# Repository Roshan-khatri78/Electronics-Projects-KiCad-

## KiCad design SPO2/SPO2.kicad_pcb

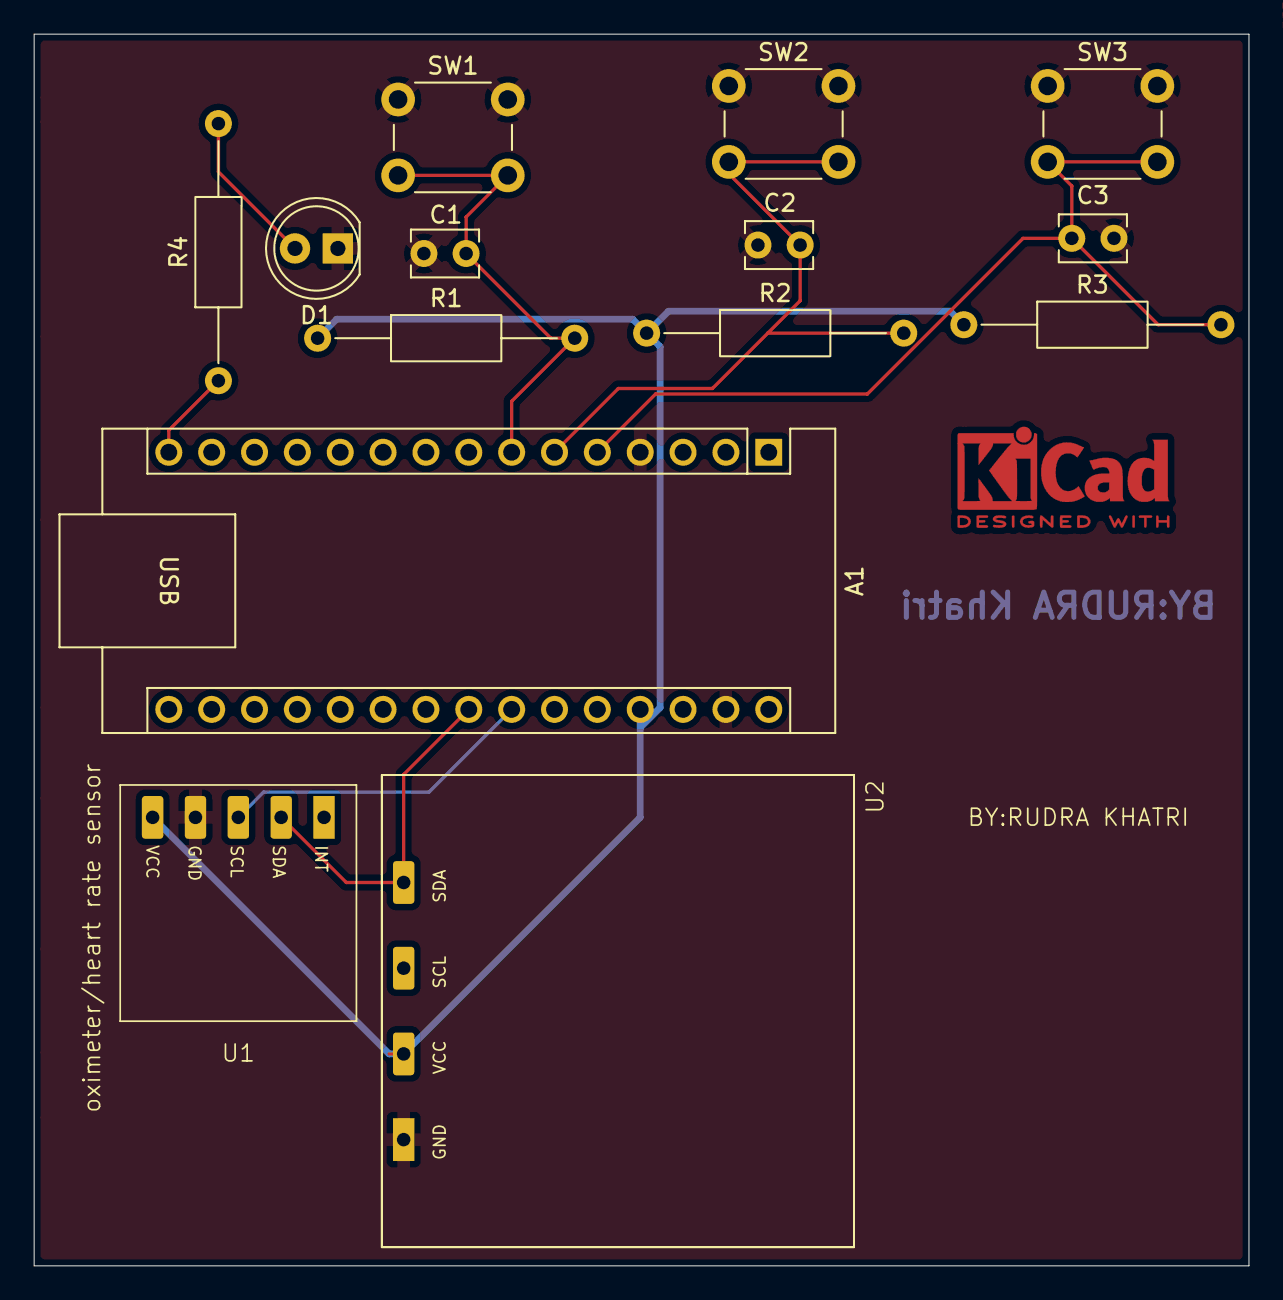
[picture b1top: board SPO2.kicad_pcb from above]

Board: 4 copper layers, 72.0 x 73.0 mm, 14 parts (0 on the bottom side), 9 nets.

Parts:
A1: Arduino_Nano_v3.x; Arduino_Nano
C1, C2, C3: 100n; C_Disc_D3.8mm_W2.6mm_P2.50mm
D1: LED; LED_D5.0mm
R1, R2, R3, R4: 1k; R_Axial_DIN0207_L6.3mm_D2.5mm_P15.24mm_Horizontal
SW1, SW2, SW3: SW_Push; SW_PUSH_6mm
U1: Max30102; MAX30102_Module
U2: SSD1306

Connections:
+5V: A1.27 (+5V), R1.1, R2.1, R3.1, U1.5 (VCC), U2.2 (VCC)
/SCL: A1.24 (A5), U1.3 (SCL)
GND: A1.4 (GND), A1.29 (GND), C1.2, C2.2, C3.2, D1.1 (K), SW1.1, SW2.1, SW3.1, U1.4 (GND), U2.1 (GND)
unnamed: A1.23 (A4), U1.2 (SDA), U2.4 (SDA)
unnamed: A1.5 (D2), C3.1, R3.2, SW3.2
unnamed: A1.6 (D3), C2.1, R2.2, SW2.2
unnamed: A1.7 (D4), C1.1, R1.2, SW1.2
unnamed: A1.15 (D12), R4.1
unnamed: D1.2 (A), R4.2

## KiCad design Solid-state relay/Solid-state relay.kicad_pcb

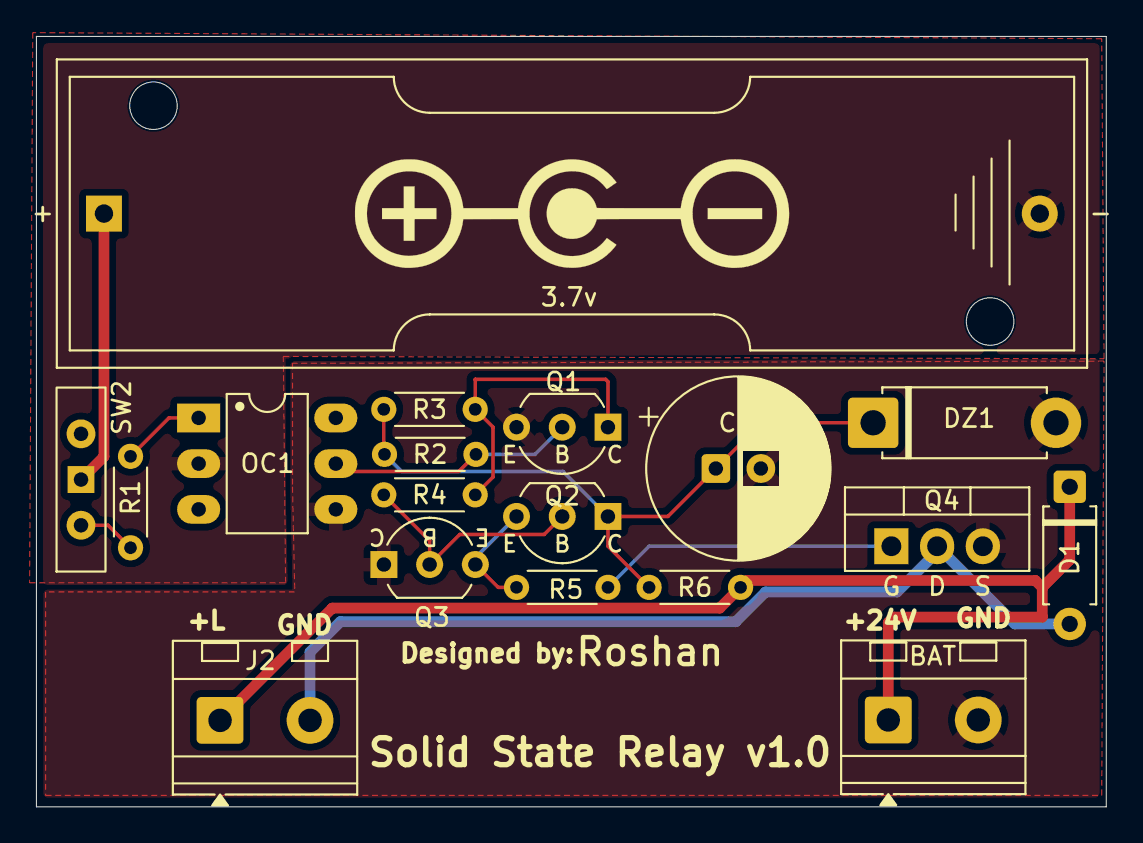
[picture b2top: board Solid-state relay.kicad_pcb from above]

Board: 4 copper layers, 59.4 x 42.8 mm, 18 parts (0 on the bottom side), 13 nets.

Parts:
3.7v: 3.7v; BatteryHolder_Keystone_2460_1xAA
BAT: Screw_Terminal_01x02; TerminalBlock_MetzConnect_Type094_RT03502HBLU_1x02_P5.00mm_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
C1: 10uf/10v; CP_Radial_D10.0mm_P2.50mm
D1: 1N4007; D_A-405_P7.62mm_Horizontal
DZ1: D_Zener_Generic; D_5W_P10.16mm_Horizontal
J2: Screw_Terminal_01x02; TerminalBlock_MetzConnect_Type094_RT03502HBLU_1x02_P5.00mm_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
OC1: MCT2EM; DIP-6_W7.62mm_LongPads
Q1: BC548; TO-92_Inline_Wide_CBE
Q2: BC547; TO-92_Inline_Wide_CBE
Q3: BC557; TO-92_Inline_Wide_CBE
Q4: IRF540; TO-220-3_Vertical_GDS
R1: 220; R_Axial_DIN0204_L3.6mm_D1.6mm_P5.08mm_Horizontal
R2: 10k; R_Axial_DIN0204_L3.6mm_D1.6mm_P5.08mm_Horizontal
R3, R4: 1k; R_Axial_DIN0204_L3.6mm_D1.6mm_P5.08mm_Horizontal
R5, R6: 100; R_Axial_DIN0204_L3.6mm_D1.6mm_P5.08mm_Horizontal
SW2: SW_Wuerth_450301014042; SW_Slide-03_Wuerth-WS-SLTV_10x2.5x6.4_P2.54mm

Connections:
/+: BAT.1, D1.1 (K), J2.1, R6.2
/A: D1.2 (A), J2.2, Q4.2 (D)
GND_CTRL: 3.7v.2 (-), OC1.2
GND_PWR: BAT.2, C1.2, DZ1.2 (A), OC1.4, Q1.3 (E), Q3.1 (C), Q4.3 (S)
unnamed: 3.7v.1 (+), SW2.1 (B)
unnamed: C1.1, DZ1.1 (K), Q2.1 (C), R2.1, R3.1, R6.1
unnamed: OC1.1, R1.2
unnamed: OC1.5, Q1.2 (B), R2.2
unnamed: Q1.1 (C), R3.2, R4.1
unnamed: Q2.2 (B), Q3.2 (B), R4.2
unnamed: Q2.3 (E), Q3.3 (E), R5.1
unnamed: Q4.1 (G), R5.2
unnamed: R1.1, SW2.2 (C)

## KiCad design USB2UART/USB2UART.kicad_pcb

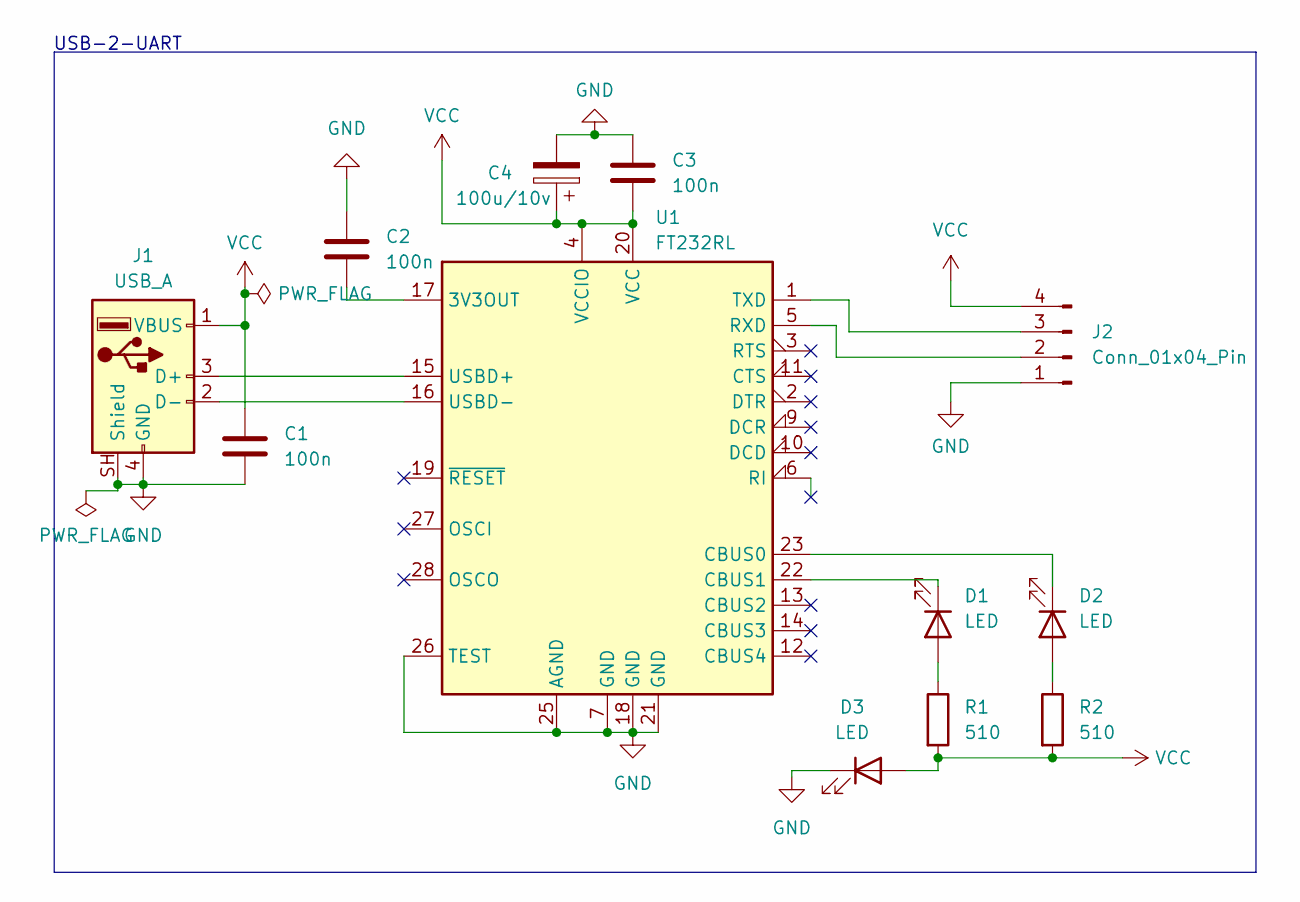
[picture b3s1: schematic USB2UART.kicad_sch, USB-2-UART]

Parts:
C1, C2, C3: 100n; C_Disc_D6.0mm_W2.5mm_P5.00mm
C4: 100u/10v; CP_Radial_D5.0mm_P2.00mm
D1, D2, D3: LED; LED_D3.0mm
J1: USB_A; USB_A_Connfly_DS1095
J2: Conn_01x04_Pin; PinHeader_1x04_P2.00mm_Vertical
R1, R2: 510; R_Axial_DIN0204_L3.6mm_D1.6mm_P5.08mm_Horizontal
U1: FT232RL; SSOP-28_5.3x10.2mm_P0.65mm

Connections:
GND: C1.2, C2.1, C3.1, C4.2, D3.1 (K), J1.4 (GND), J1.SH (Shield), J2.1, U1.7 (GND), U1.18 (GND), U1.21 (GND), U1.25 (AGND), U1.26 (TEST)
unnamed: D1.2 (A), R1.1
unnamed: D1.1 (K), U1.22 (CBUS1)
unnamed: D2.2 (A), R2.1
unnamed: D2.1 (K), U1.23 (CBUS0)
unnamed: J1.3 (D+), U1.15 (USBD+)
unnamed: J1.2 (D-), U1.16 (USBD-)
unnamed: J2.2, U1.5 (RXD)
unnamed: J2.3, U1.1 (TXD)
unnamed: C2.2, U1.17 (3V3OUT)
VCC: C1.1, C3.2, C4.1, D3.2 (A), J1.1 (VBUS), J2.4, R1.2, R2.2, U1.4 (VCCIO), U1.20 (VCC)

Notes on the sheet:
USB-2-UART

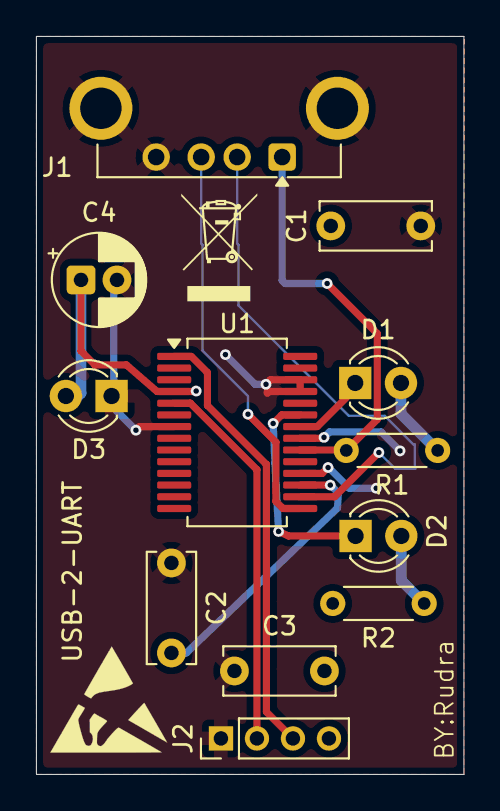
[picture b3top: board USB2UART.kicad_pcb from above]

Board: 4 copper layers, 23.8 x 41.0 mm, 12 parts (0 on the bottom side), 11 nets.

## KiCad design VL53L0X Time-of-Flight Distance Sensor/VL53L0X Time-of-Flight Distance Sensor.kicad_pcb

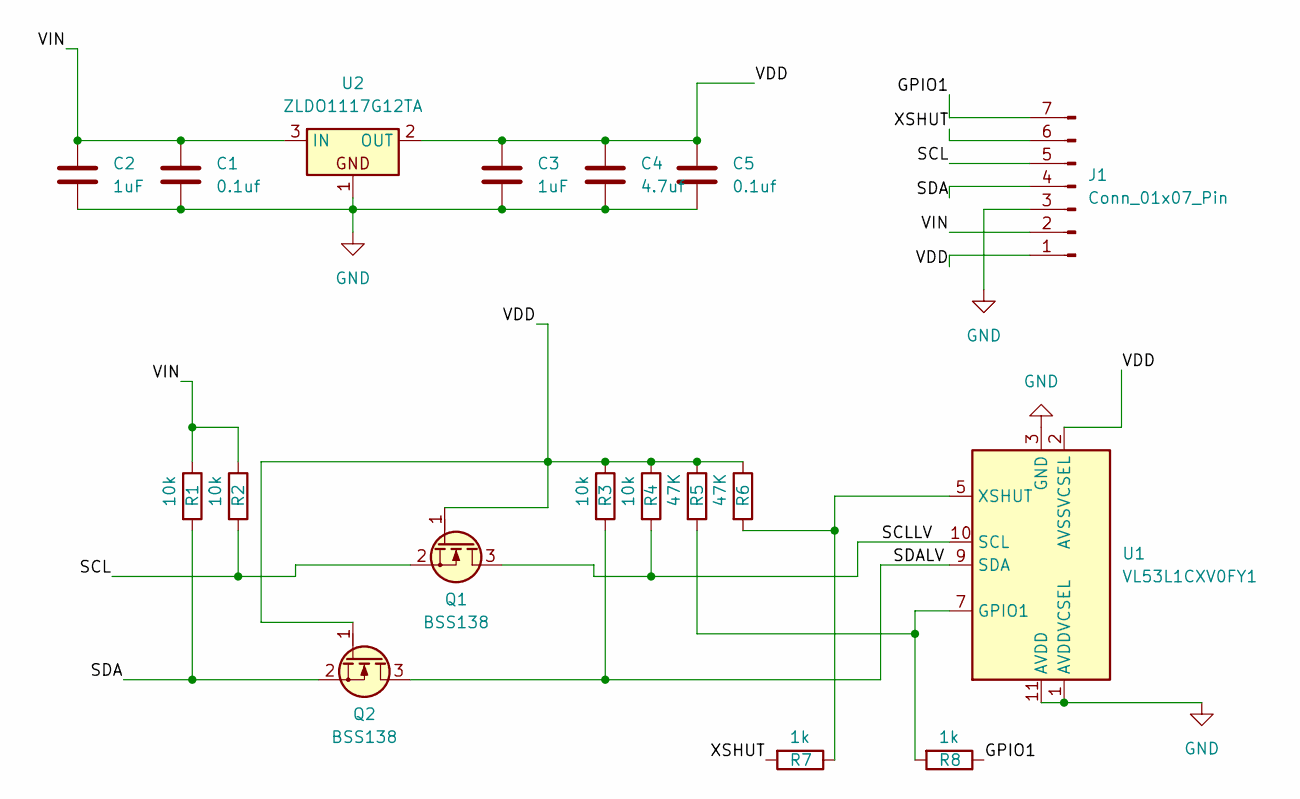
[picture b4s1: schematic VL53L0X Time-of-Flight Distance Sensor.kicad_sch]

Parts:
C1, C5: 0.1uf; C_0402_1005Metric_Pad0.74x0.62mm_HandSolder
C2, C3: 1uF; C_0402_1005Metric_Pad0.74x0.62mm_HandSolder
C4: 4.7uf; C_0402_1005Metric_Pad0.74x0.62mm_HandSolder
J1: Conn_01x07_Pin; PinHeader_1x07_P2.54mm_Horizontal
Q1, Q2: BSS138; SOT-23
R1, R2, R3, R4: 10k; R_0201_0603Metric
R5, R6: 47K; R_0201_0603Metric
R7, R8: 1k; R_0805_2012Metric
U1: VL53L1CXV0FY1; ST_VL53L1x
U2: ZLDO1117G12TA; SOT-323_SC-70

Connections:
/GPIO1: J1.7, R8.1
/SCL: J1.5, Q1.2 (S), R2.2
/SCLLV: Q1.3 (D), R4.2, U1.10 (SCL)
/SDA: J1.4, Q2.2 (S), R1.2
/SDALV: Q2.3 (D), R3.2, U1.9 (SDA)
/VDD: C3.1, C4.1, C5.1, J1.1, Q1.1 (G), Q2.1 (G), R3.1, R4.1, R5.1, R6.1, U1.2 (AVSSVCSEL), U2.2 (OUT)
/VIN: C1.1, C2.1, J1.2, R1.1, R2.1, U2.3 (IN)
/XSHUT: J1.6, R7.2
GND: C1.2, C2.2, C3.2, C4.2, C5.2, J1.3, U1.1 (AVDDVCSEL), U1.3 (GND), U1.4 (GND), U1.6 (GND), U1.11 (AVDD), U1.12 (GND), U2.1
unnamed: R5.2, R8.2, U1.7 (GPIO1)
unnamed: R6.2, R7.1, U1.5 (XSHUT)

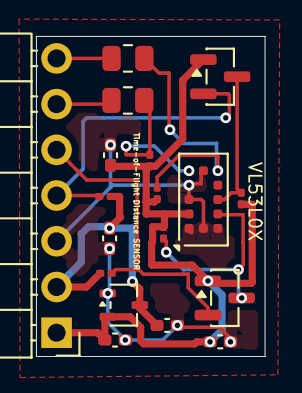
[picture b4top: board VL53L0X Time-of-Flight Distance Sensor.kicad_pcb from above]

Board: 2 copper layers, 12.7 x 17.8 mm, 18 parts (0 on the bottom side), 11 nets.

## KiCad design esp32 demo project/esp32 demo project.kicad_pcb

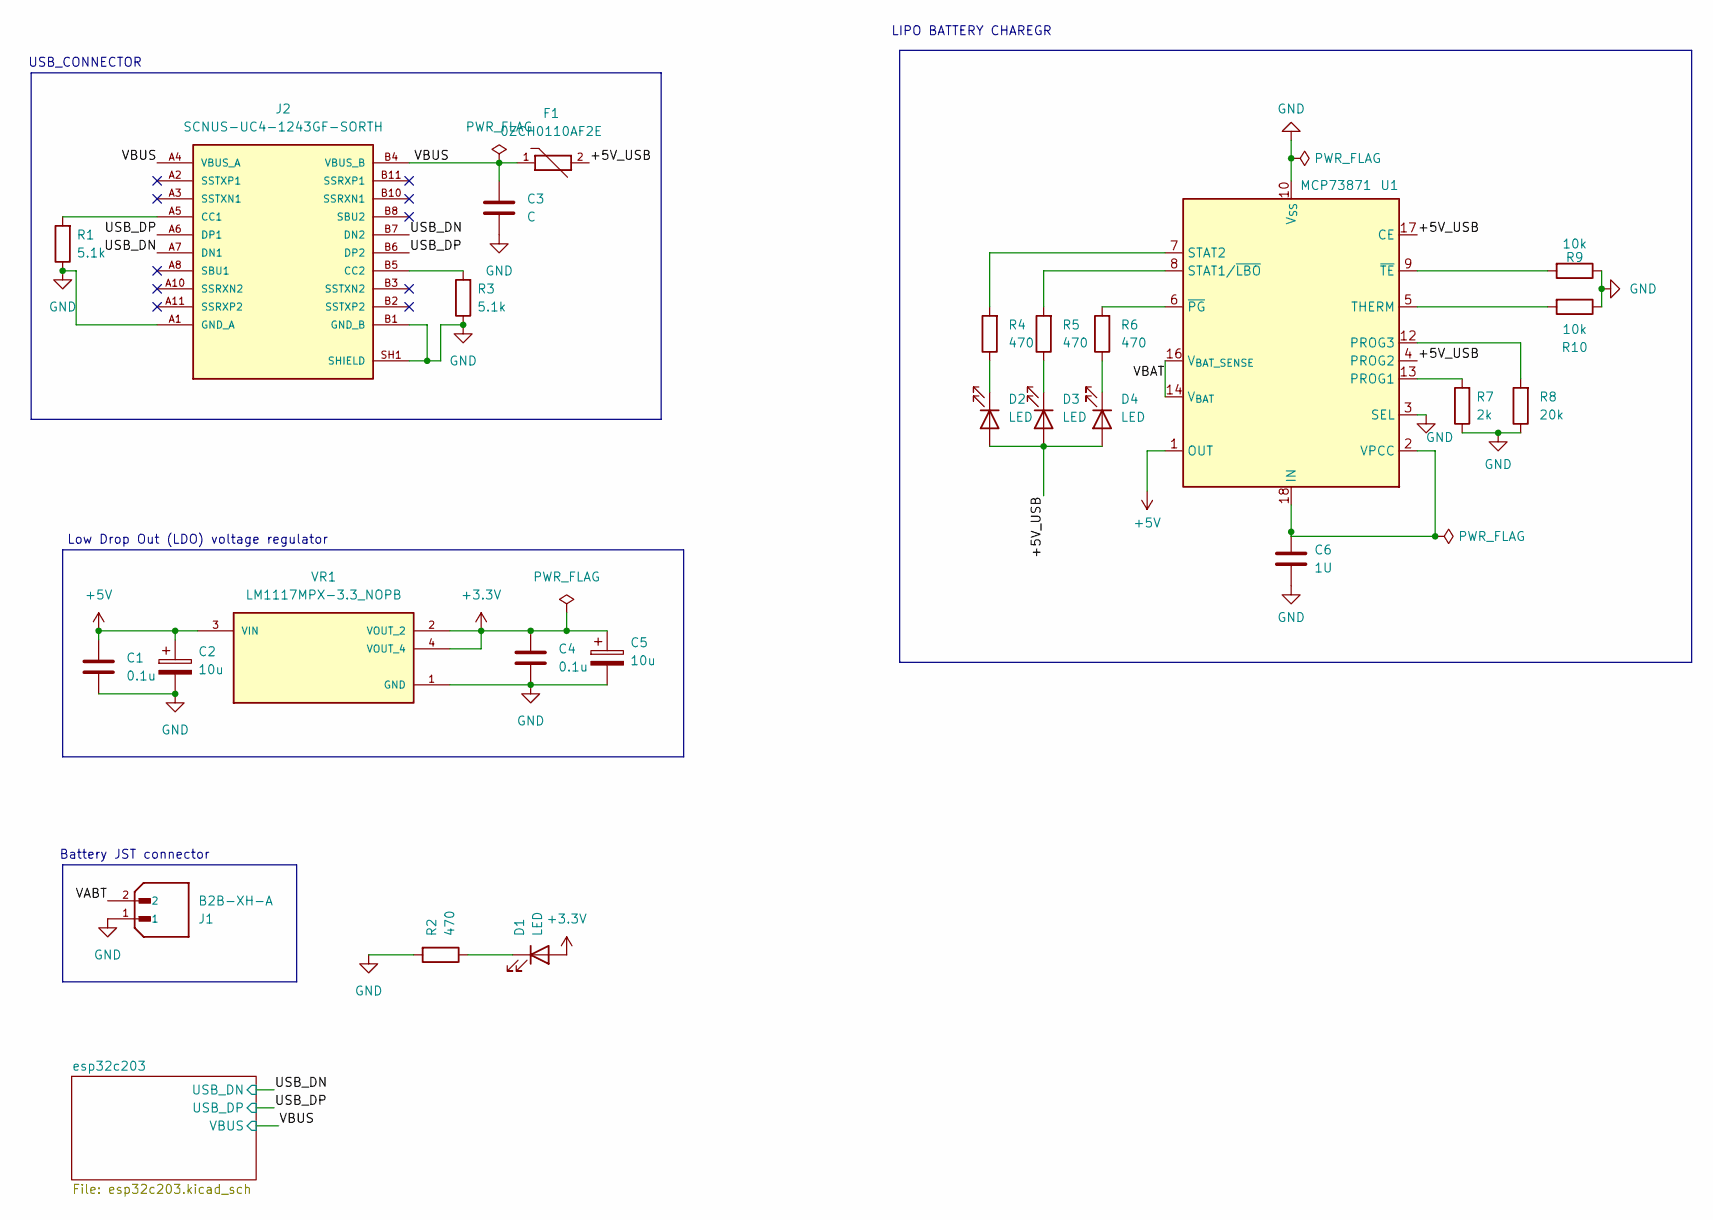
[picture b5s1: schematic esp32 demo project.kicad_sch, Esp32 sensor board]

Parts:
C1, C4: 0.1u; C_0805_2012Metric
C2, C5: 10u; CP_EIA-3216-18_Kemet-A
C3: C; C_0805_2012Metric
C6: 1U; C_0805_2012Metric
D1, D2, D3, D4: LED; LED_0805_2012Metric
F1: 0ZCH0110AF2E; FUSC3225X100N; PARTREV Apr2023
J1: B2B-XH-A; JST_B2B-XH-A; PARTREV N/A
J2: SCNUS-UC4-1243GF-SORTH; SUNTSU_SCNUS-UC4-1243GF-SORTH; PARTREV 06/08/2022
R1, R3: 5.1k; R_0805_2012Metric
R2, R4, R5, R6: 470; R_0805_2012Metric
R7: 2k; R_0805_2012Metric
R8: 20k; R_0805_2012Metric
R9, R10: 10k; R_0805_2012Metric
U1: MCP73871; QFN-20-1EP_4x4mm_P0.5mm_EP2.5x2.5mm
VR1: LM1117MPX-3.3_NOPB; VREG_LM1117MPX-3.3_NOPB; PARTREV O

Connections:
+3.3V: C1.2, C2.2, C3.2, C4.1, C4.2, C5.1, C5.2, C6.2, D1.2 (A), J1.1, J2.A1 (GND_A), J2.A12 (GND_A), J2.B1 (GND_B), J2.B12 (GND_B), J2.SH1 (SHIELD), J2.SH2 (SHIELD), J2.SH3 (SHIELD), J2.SH4 (SHIELD), R1.1, R2.2, R3.1, R7.1, R8.1, R9.1, R10.1, U1.3 (SEL), U1.10 (V_{SS}), U1.11 (V_{SS}), U1.21 (V_{SS}), VR1.1 (GND), VR1.2 (VOUT_2), VR1.4 (VOUT_4); also elsewhere on the board
+5V: C1.1, C2.1, U1.1 (OUT), U1.20 (OUT), VR1.3 (VIN)
/+5V_USB: D2.2 (A), D3.2 (A), D4.2 (A), F1.2, U1.4 (PROG2), U1.17 (CE)
/USB_DN: J2.A7 (DN1), J2.B7 (DN2); also elsewhere on the board
/USB_DP: J2.A6 (DP1), J2.B6 (DP2); also elsewhere on the board
/VABT: J1.2
/VBAT: U1.14 (V_{BAT}), U1.15 (V_{BAT}), U1.16 (V_{BAT_SENSE})
unnamed: D1.1 (K), R2.1
unnamed: D2.1 (K), R4.1
unnamed: D3.1 (K), R5.1
unnamed: D4.1 (K), R6.1
unnamed: J2.A5 (CC1), R1.2
unnamed: J2.B5 (CC2), R3.2
unnamed: R7.2, U1.13 (PROG1)
unnamed: R8.2, U1.12 (PROG3)
unnamed: R5.2, U1.8 (STAT1/~LBO)
unnamed: R4.2, U1.7 (STAT2)
unnamed: R10.2, U1.5 (THERM)
unnamed: C6.1, U1.2 (VPCC), U1.18 (IN), U1.19 (IN)
unnamed: R6.2, U1.6 (~PG)
unnamed: R9.2, U1.9 (~TE)
VBUS_A: C3.1, F1.1, J2.A4 (VBUS_A), J2.A9 (VBUS_A), J2.B4 (VBUS_B), J2.B9 (VBUS_B); also elsewhere on the board

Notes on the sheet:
USB_CONNECTOR
Battery JST connector
Low Drop Out (LDO) voltage regulator
LIPO BATTERY CHAREGR

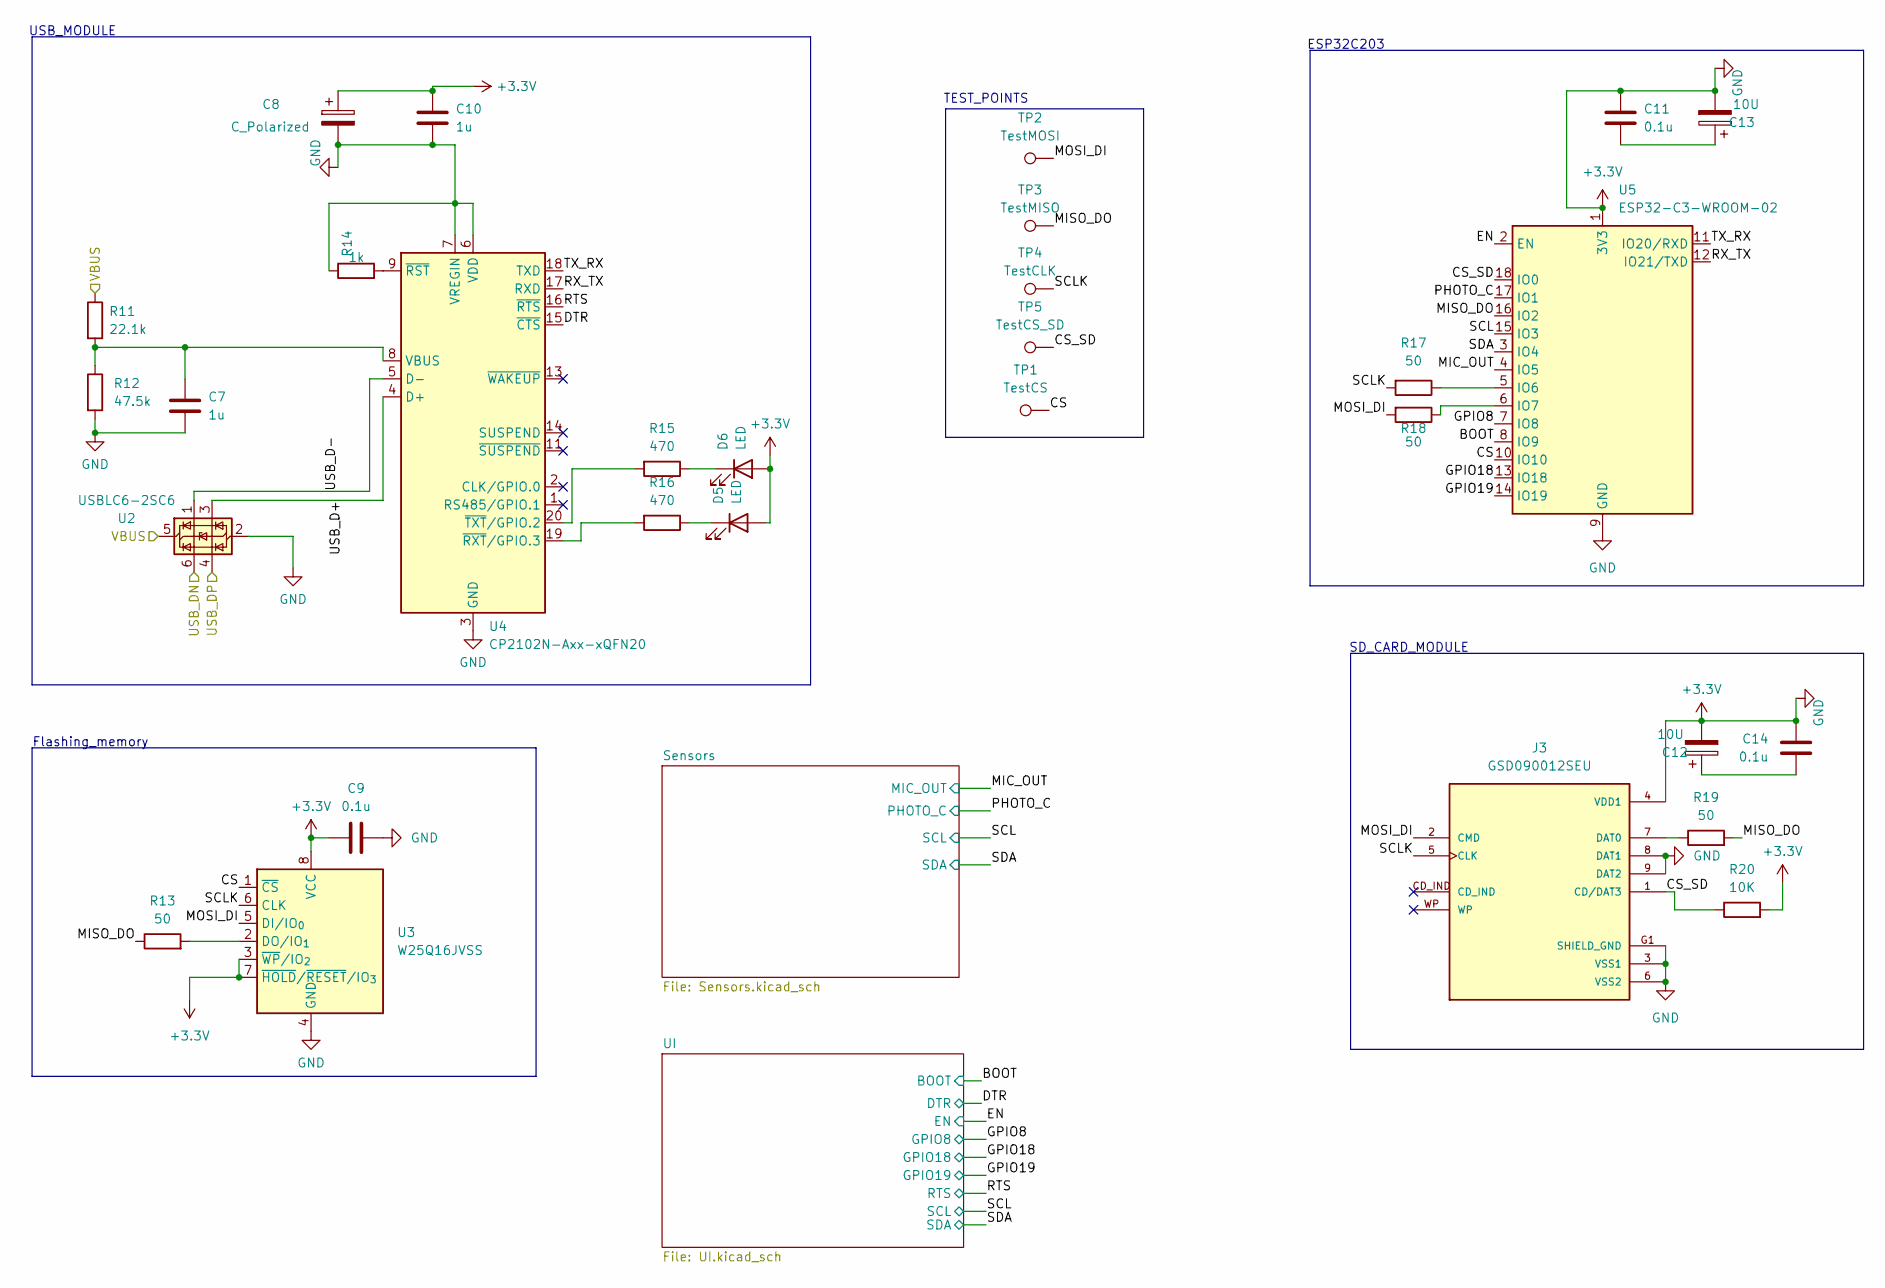
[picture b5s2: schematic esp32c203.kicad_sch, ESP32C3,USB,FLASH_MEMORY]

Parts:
C7, C10: 1u; C_0805_2012Metric
C8: C_Polarized; CP_EIA-3216-18_Kemet-A
C9, C11, C14: 0.1u; C_0805_2012Metric
C12, C13: 10U; CP_EIA-3216-18_Kemet-A
D5, D6: LED; LED_0805_2012Metric
J3: GSD090012SEU; AMPHENOL_GSD090012SEU; PARTREV E
R11: 22.1k; R_0805_2012Metric
R12: 47.5k; R_0805_2012Metric
R13, R17, R18, R19: 50; R_0805_2012Metric
R14: 1k; R_0805_2012Metric
R15, R16: 470; R_0805_2012Metric
R20: 10K; R_0805_2012Metric
TP1: TestCS; TestPoint_Pad_D1.0mm
TP2: TestMOSI; TestPoint_Pad_D1.0mm
TP3: TestMISO; TestPoint_Pad_D1.0mm
TP4: TestCLK; TestPoint_Pad_D1.0mm
TP5: TestCS_SD; TestPoint_Pad_D1.0mm
U2: USBLC6-2SC6; SOT-23-6
U3: W25Q16JVSS; SOIC-8_5.3x5.3mm_P1.27mm
U4: CP2102N-Axx-xQFN20; SiliconLabs_QFN-20-1EP_3x3mm_P0.5mm_EP1.8x1.8mm
U5: ESP32-C3-WROOM-02

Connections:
+3.3V: C7.2, C8.1, C8.2, C9.1, C9.2, C10.1, C10.2, C11.2, C12.2, C13.2, C14.2, D5.2 (A), D6.2 (A), J3.3 (VSS1), J3.4 (VDD1), J3.6 (VSS2), J3.8 (DAT1), J3.9 (DAT2), J3.G1 (SHIELD_GND), J3.G2 (SHIELD_GND), J3.G3 (SHIELD_GND), J3.G4 (SHIELD_GND), R12.2, R14.1, R20.2, U2.2 (GND), U3.3 (~WP/IO_{2}), U3.4 (GND), U3.7 (~HOLD/~RESET/IO_{3}), U3.8 (VCC), U4.3 (GND), U4.6 (VDD), U4.7 (VREGIN), U4.12 (GND), U4.21 (GND), U5.1 (3V3), U5.9 (GND), U5.19 (GND); also elsewhere on the board
/USB_DN: U2.6 (I/O1); also elsewhere on the board
/USB_DP: U2.4 (I/O2); also elsewhere on the board
/esp32c203/BOOT: U5.8 (IO9); also elsewhere on the board
/esp32c203/CS: TP1.1 (1_1), U3.1 (~CS), U5.10 (IO10)
/esp32c203/CS_SD: J3.1 (CD/DAT3), R20.1, TP5.1 (1_1), U5.18 (IO0)
/esp32c203/DTR: U4.15 (~CTS); also elsewhere on the board
/esp32c203/EN: U5.2 (EN); also elsewhere on the board
/esp32c203/GPIO8: U5.7 (IO8); also elsewhere on the board
/esp32c203/GPIO18: U5.13 (IO18); also elsewhere on the board
/esp32c203/GPIO19: U5.14 (IO19); also elsewhere on the board
/esp32c203/MIC_OUT: U5.4 (IO5); also elsewhere on the board
/esp32c203/MISO_DO: R13.1, R19.2, TP3.1 (1_1), U5.16 (IO2)
/esp32c203/MOSI_DI: J3.2 (CMD), R18.2, TP2.1 (1_1), U3.5 (DI/IO_{0})
/esp32c203/PHOTO_C: U5.17 (IO1); also elsewhere on the board
/esp32c203/RTS: U4.16 (~RTS); also elsewhere on the board
/esp32c203/RX_TX: U4.17 (RXD), U5.12 (IO21/TXD)
/esp32c203/SCL: U5.15 (IO3); also elsewhere on the board
/esp32c203/SCLK: J3.5 (CLK), R17.2, TP4.1 (1_1), U3.6 (CLK)
/esp32c203/SDA: U5.3 (IO4); also elsewhere on the board
/esp32c203/TX_RX: U4.18 (TXD), U5.11 (IO20/RXD)
/esp32c203/USB_D+: U2.3 (I/O2), U4.4 (D+)
/esp32c203/USB_D-: U2.1 (I/O1), U4.5 (D-)
unnamed: C11.1, C13.1
unnamed: C12.1, C14.1
unnamed: D5.1 (K), R16.1
unnamed: D6.1 (K), R15.1
unnamed: J3.7 (DAT0), R19.1
unnamed: R13.2, U3.2 (DO/IO_{1})
unnamed: C7.1, R11.2, R12.1, U4.8 (VBUS)
unnamed: R14.2, U4.9 (~RST)
unnamed: R16.2, U4.19 (~RXT/GPIO.3)
unnamed: R15.2, U4.20 (~TXT/GPIO.2)
unnamed: R17.1, U5.5 (IO6)
unnamed: R18.1, U5.6 (IO7)
VBUS_A: R11.1, U2.5 (VBUS); also elsewhere on the board

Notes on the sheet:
Flashing_memory
TEST_POINTS
SD_CARD_MODULE
USB_MODULE
ESP32C203

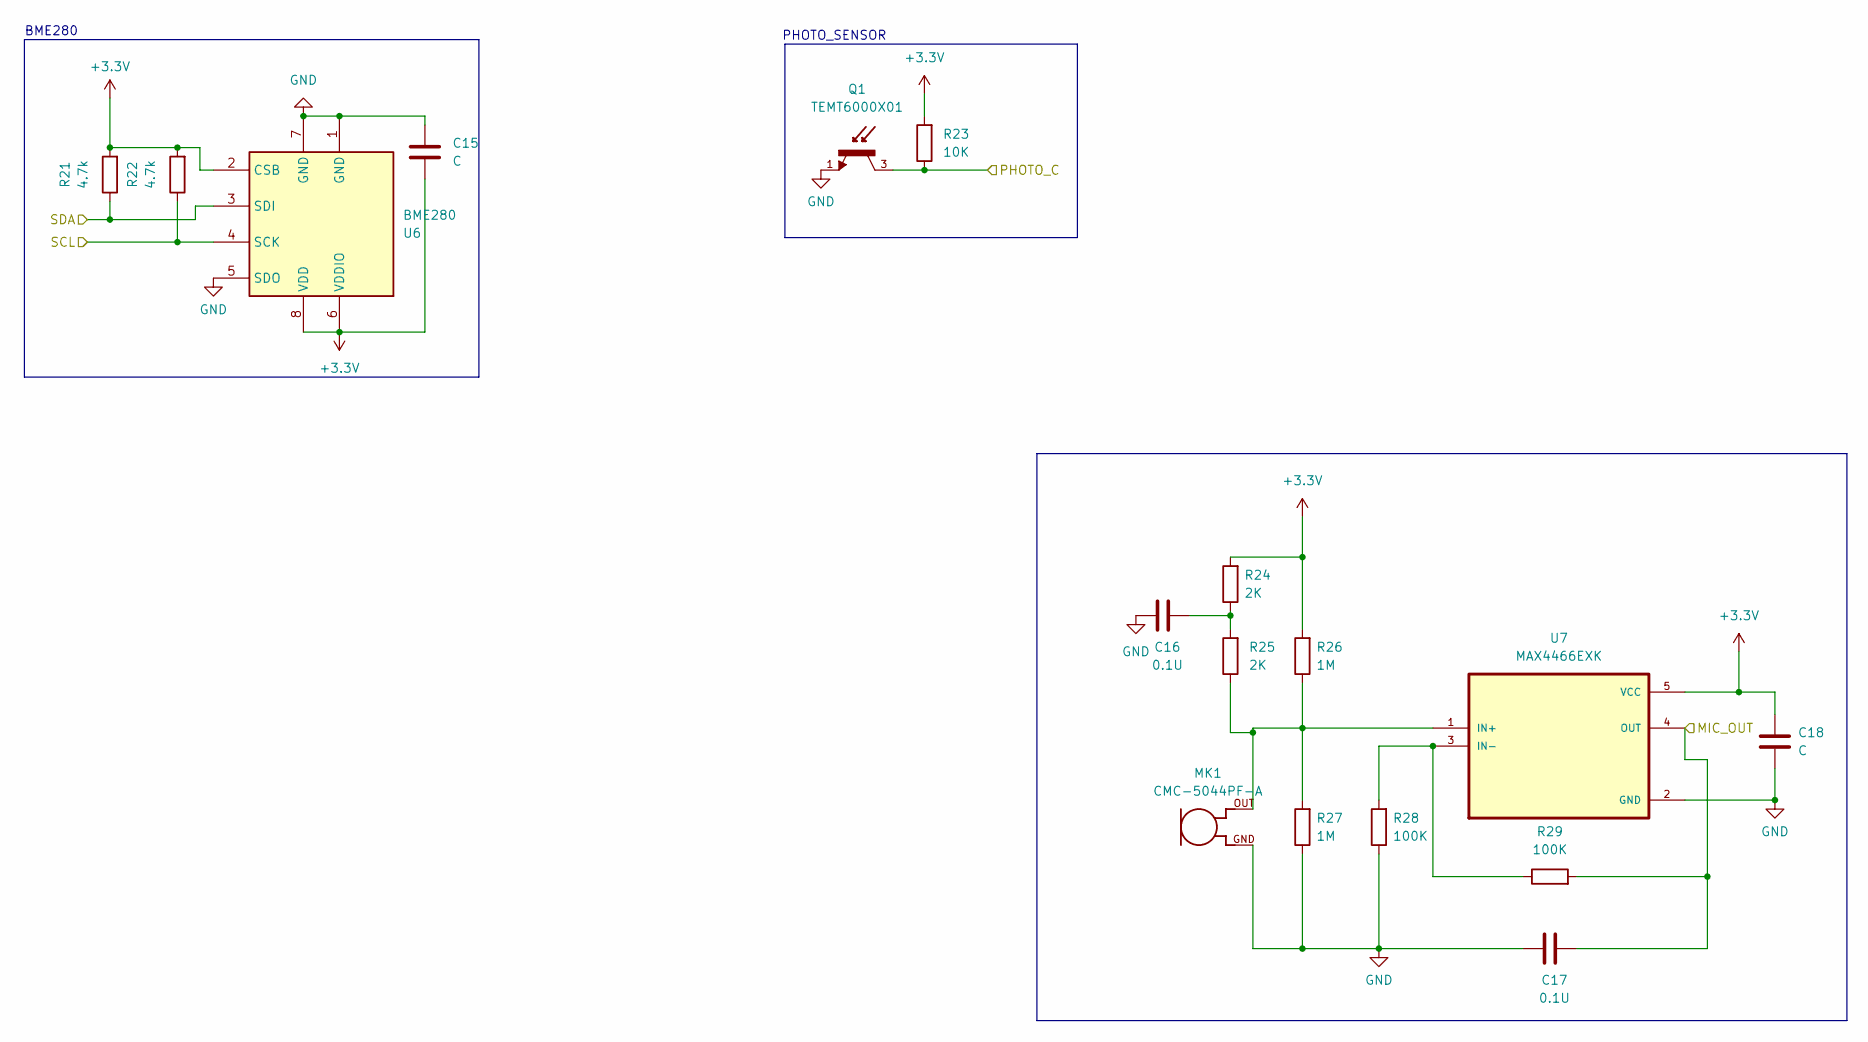
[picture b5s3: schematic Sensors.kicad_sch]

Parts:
C15, C18: C; C_0805_2012Metric
C16, C17: 0.1U; C_0805_2012Metric
MK1: CMC-5044PF-A; CUI_CMC-5044PF-A
Q1: TEMT6000X01; TRANS_TEMT6000X01; PARTREV 1.9
R21, R22: 4.7k; R_0805_2012Metric
R23: 10K; R_0805_2012Metric
R24, R25: 2K; R_0805_2012Metric
R26, R27: 1M; R_0805_2012Metric
R28, R29: 100K; R_0805_2012Metric
U6: BME280; Bosch_LGA-8_2.5x2.5mm_P0.65mm_ClockwisePinNumbering
U7: MAX4466EXK; SOT65P210X110-5N

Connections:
+3.3V: C15.1, C15.2, C16.1, C17.1, C18.1, C18.2, MK1.GND, Q1.1, R21.2, R22.2, R23.2, R24.2, R26.2, R27.1, R28.1, U6.1 (GND), U6.2 (CSB), U6.5 (SDO), U6.6 (VDDIO), U6.7 (GND), U6.8 (VDD), U7.2 (GND), U7.5 (VCC); also elsewhere on the board
/esp32c203/MIC_OUT: C17.2, R29.2, U7.4 (OUT); also elsewhere on the board
/esp32c203/PHOTO_C: Q1.3, R23.1; also elsewhere on the board
/esp32c203/SCL: R22.1, U6.4 (SCK); also elsewhere on the board
/esp32c203/SDA: R21.1, U6.3 (SDI); also elsewhere on the board
unnamed: C16.2, R24.1, R25.2
unnamed: MK1.OUT, R25.1, R26.1, R27.2, U7.1 (IN+)
unnamed: R28.2, R29.1, U7.3 (IN-)

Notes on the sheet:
PHOTO_SENSOR
BME280

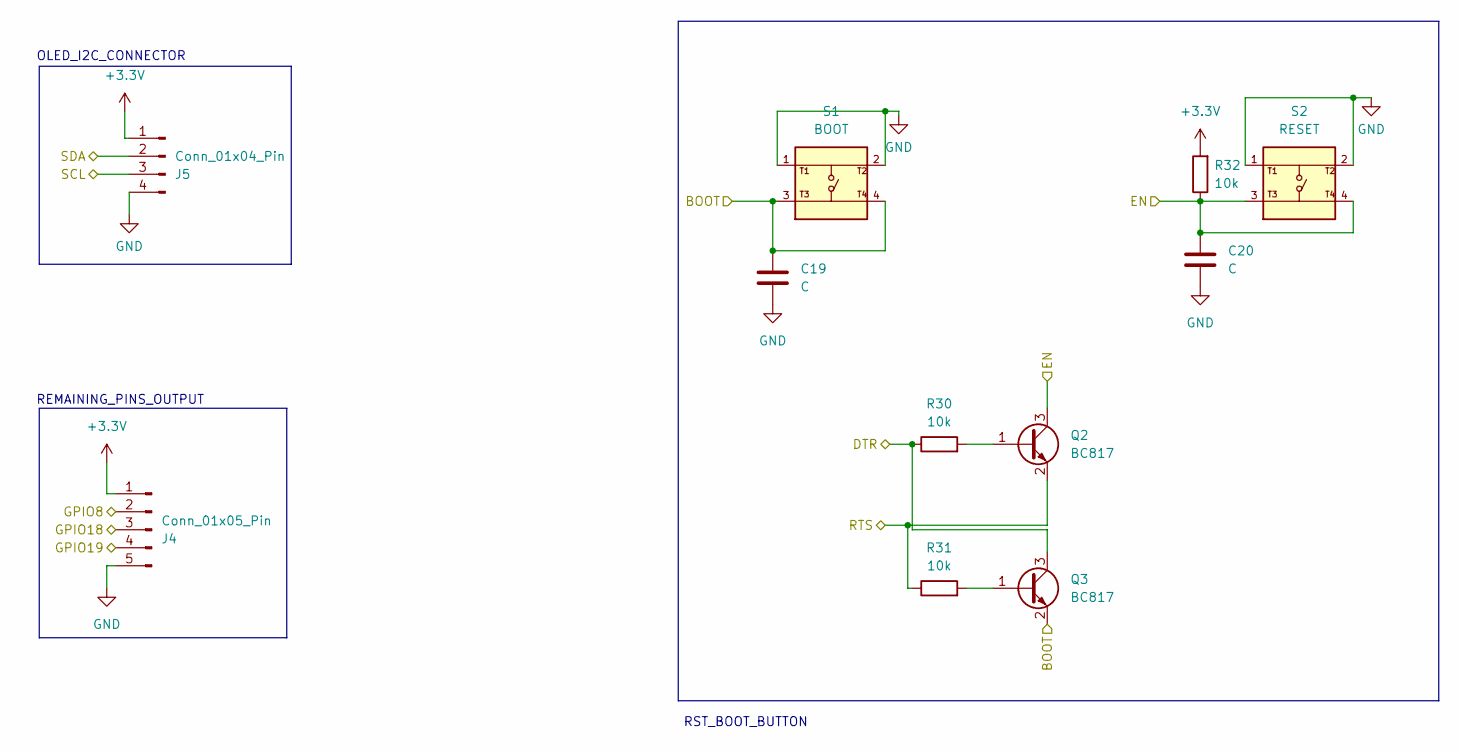
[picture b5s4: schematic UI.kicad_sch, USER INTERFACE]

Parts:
C19, C20: C; C_0805_2012Metric
J4: Conn_01x05_Pin; PinHeader_1x05_P2.54mm_Vertical
J5: Conn_01x04_Pin; PinHeader_1x04_P2.54mm_Vertical
Q2, Q3: BC817; SOT-23
R30, R31, R32: 10k; R_0805_2012Metric
S1: BOOT; SW_USLPT2819DT2TR; PARTREV P
S2: RESET; SW_USLPT2819DT2TR; PARTREV P

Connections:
+3.3V: C19.2, C20.2, J4.1, J4.5, J5.1, J5.4, R32.2, S1.1, S1.2, S2.1, S2.2; also elsewhere on the board
/esp32c203/BOOT: C19.1, Q3.2 (E), S1.3, S1.4; also elsewhere on the board
/esp32c203/DTR: Q3.3 (C), R30.1; also elsewhere on the board
/esp32c203/EN: C20.1, Q2.3 (C), R32.1, S2.3, S2.4; also elsewhere on the board
/esp32c203/GPIO8: J4.2; also elsewhere on the board
/esp32c203/GPIO18: J4.3; also elsewhere on the board
/esp32c203/GPIO19: J4.4; also elsewhere on the board
/esp32c203/RTS: Q2.2 (E), R31.1; also elsewhere on the board
/esp32c203/SCL: J5.3; also elsewhere on the board
/esp32c203/SDA: J5.2; also elsewhere on the board
unnamed: Q2.1 (B), R30.2
unnamed: Q3.1 (B), R31.2

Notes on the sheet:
REMAINING_PINS_OUTPUT
RST_BOOT_BUTTON
OLED_I2C_CONNECTOR

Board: 4 copper layers, 83 parts (0 on the bottom side), 58 nets, no tracks yet.

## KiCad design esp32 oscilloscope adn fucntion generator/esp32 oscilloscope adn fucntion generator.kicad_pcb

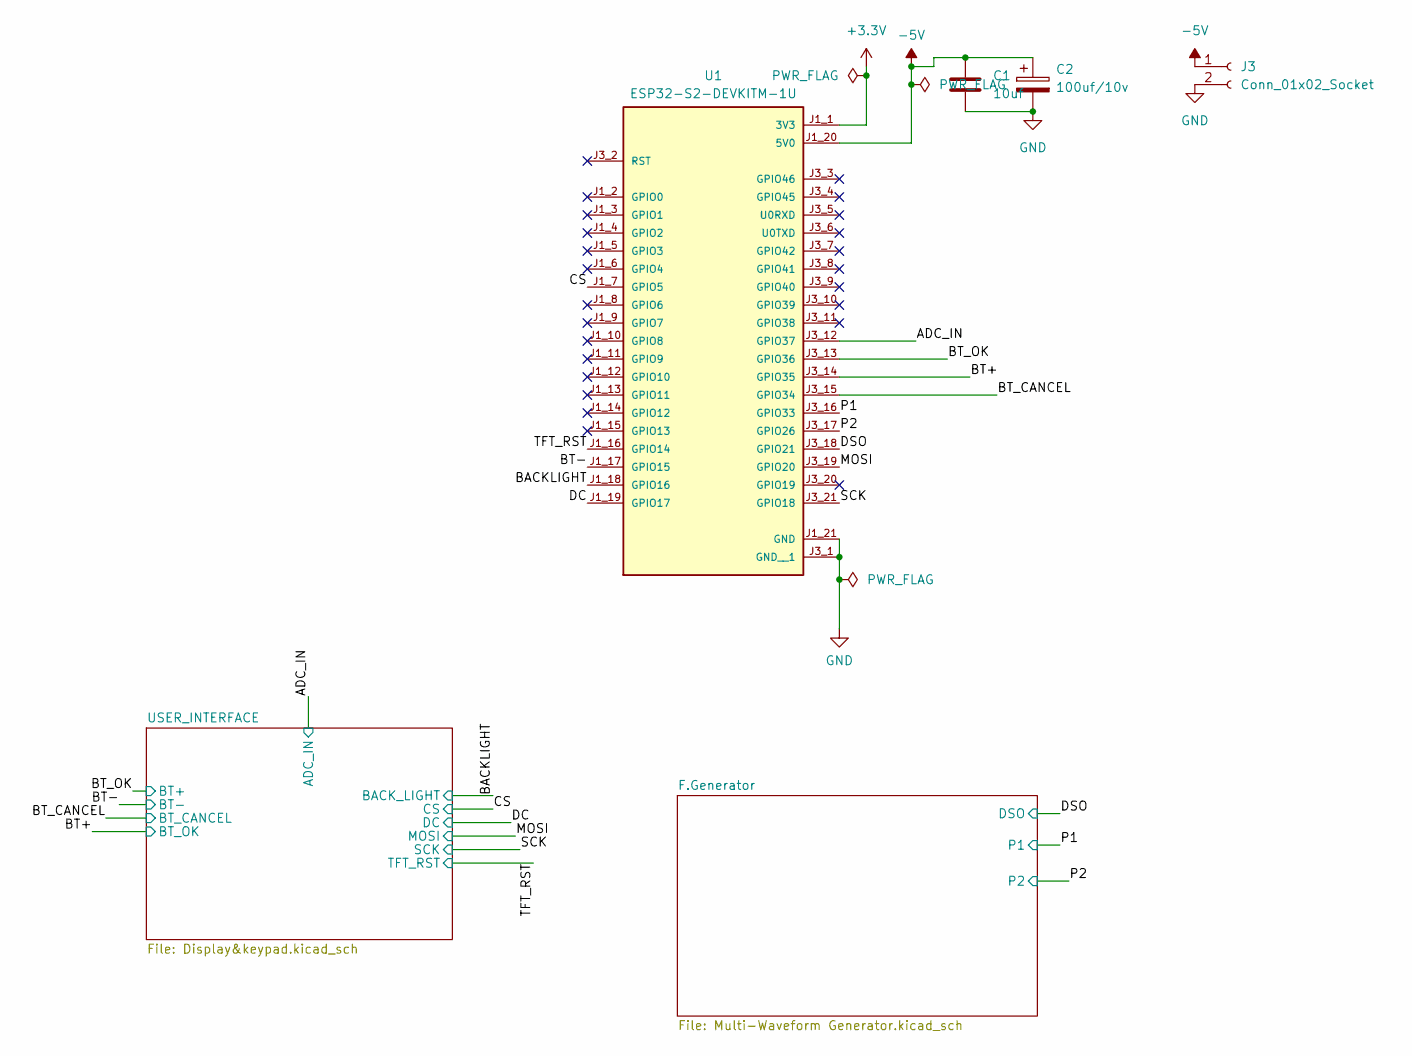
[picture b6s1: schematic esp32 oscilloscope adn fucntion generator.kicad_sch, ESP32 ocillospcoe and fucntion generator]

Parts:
C1: 10uf; C_1210_3225Metric
C2: 100uf/10v; CP_EIA-1608-08_AVX-J
J3: Conn_01x02_Socket; PinSocket_1x02_P2.00mm_Vertical
U1: ESP32-S2-DEVKITM-1U; XCVR_ESP32-S2-DEVKITM-1U; PARTREV 1.0

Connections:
+3.3V: U1.J1_1 (3V3); also elsewhere on the board
-5V: C1.1, C2.1, J3.1, U1.J1_20 (5V0)
/ADC_IN: U1.J3_12 (GPIO37); also elsewhere on the board
/BACKLIGHT: U1.J1_18 (GPIO16); also elsewhere on the board
/BT+: U1.J3_14 (GPIO35); also elsewhere on the board
/BT-: U1.J1_17 (GPIO15); also elsewhere on the board
/BT_CANCEL: U1.J3_15 (GPIO34); also elsewhere on the board
/BT_OK: U1.J3_13 (GPIO36); also elsewhere on the board
/CS: U1.J1_7 (GPIO5); also elsewhere on the board
/DC: U1.J1_19 (GPIO17); also elsewhere on the board
/DSO: U1.J3_18 (GPIO21); also elsewhere on the board
/MOSI: U1.J3_19 (GPIO20); also elsewhere on the board
/P1: U1.J3_16 (GPIO33); also elsewhere on the board
/P2: U1.J3_17 (GPIO26); also elsewhere on the board
/SCK: U1.J3_21 (GPIO18); also elsewhere on the board
/TFT_RST: U1.J1_16 (GPIO14); also elsewhere on the board
GND: C1.2, C2.2, J3.2, U1.J1_21 (GND), U1.J3_1 (GND__1); also elsewhere on the board
